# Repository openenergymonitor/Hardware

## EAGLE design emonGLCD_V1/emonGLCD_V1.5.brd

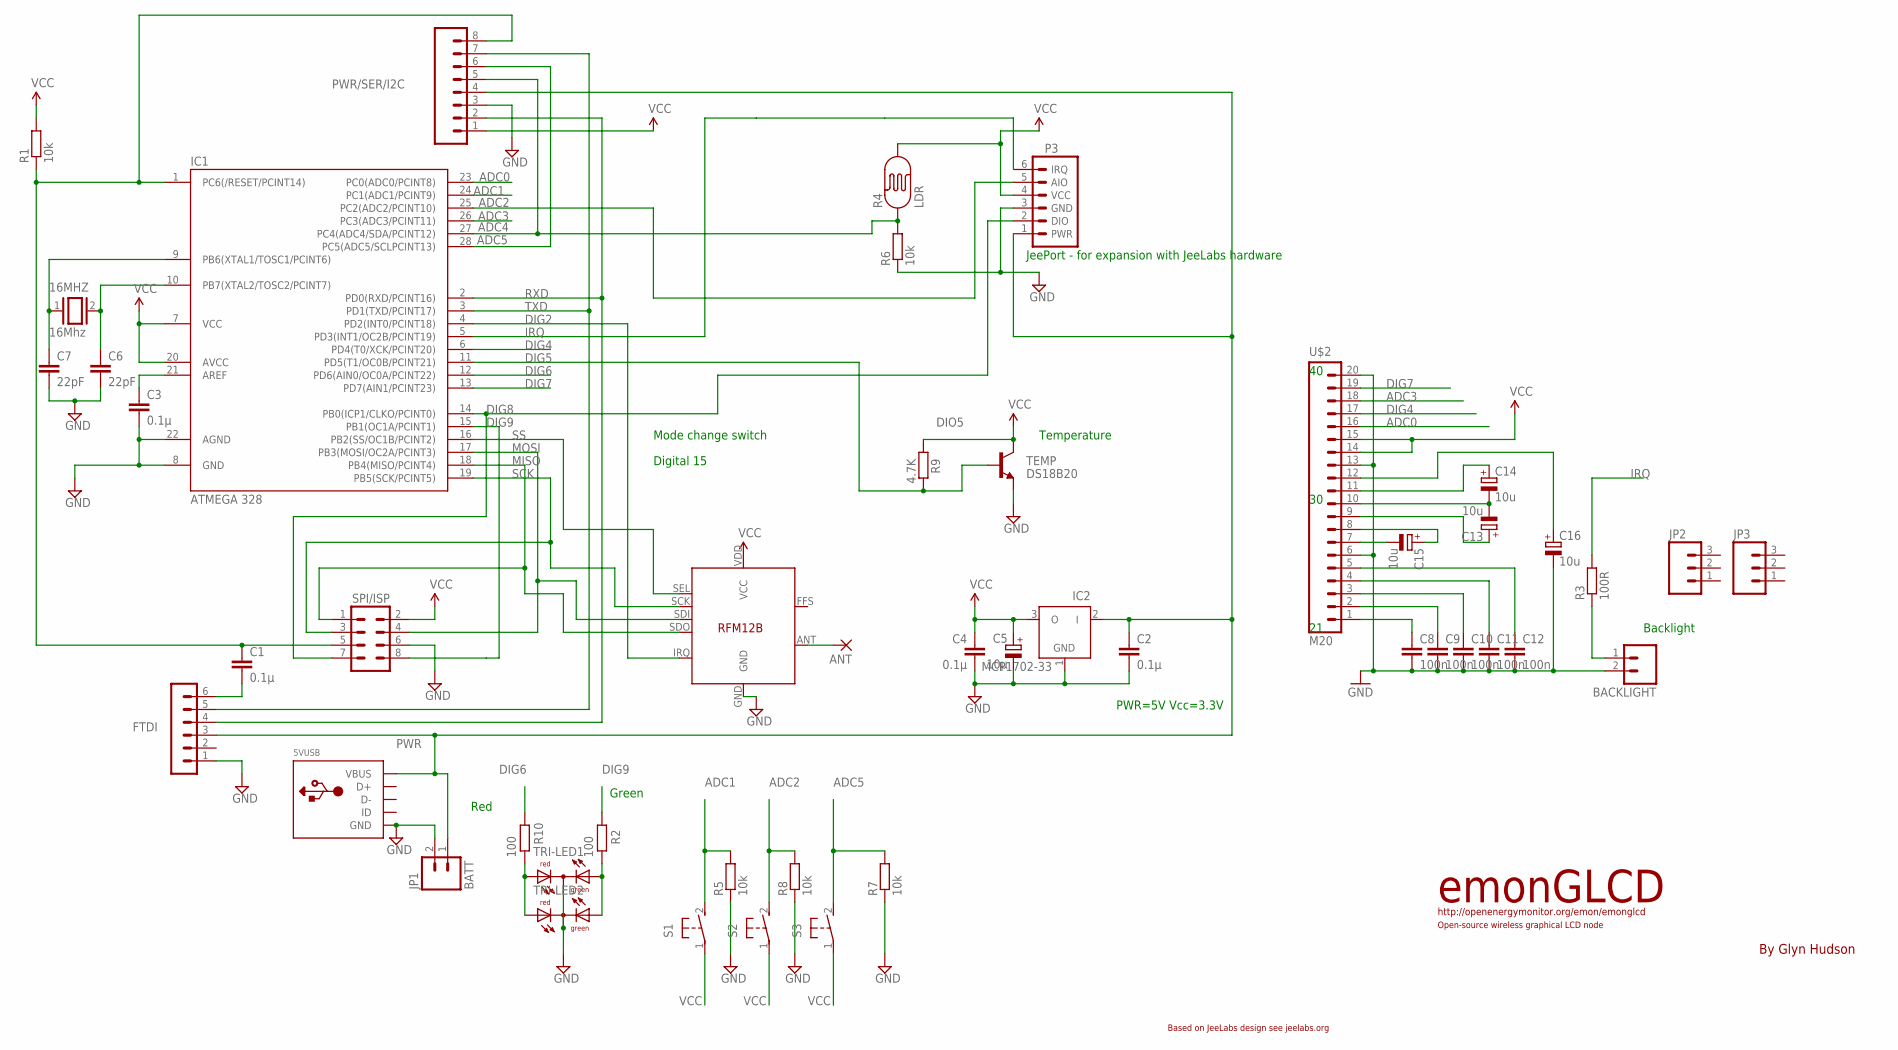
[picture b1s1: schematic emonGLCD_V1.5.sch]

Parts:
5VUSB: USBMOLEX; USB-MINIB-THM-MOLEX
16MHZ: 16Mhz; QS
ANT: 1,6/0,8
BACKLIGHT: M02PTH; 1X02
C1, C2, C3, C4: 0.1µ; C025-024X044
C5: 10µ; E1,8-4
C6, C7: 22pF; C2.5-2
C8, C9, C10, C11, C12: 100n; C2.5-2
C13, C14, C15, C16: 10u; E1,8-4
FTDI: FTDI; MA06-1
IC1: ATMEGA 328; DIL28-3
IC2: MCP1702-33; TO92
JP1: BATT; 1X02_LOCK_LONGPADS
JP2, JP3: M03PTH; 1X03
P3: JEEPORT; PORT6PIN
PWR/SER/I2C: M08; 1X08
R1, R5, R6, R7, R8: 10k; 0204/7
R2, R10: 100; 0204/7
R3: 100R; 0204/7
R4: LDR; PHOTOCELL
R9: 4.7K; 0204/7
S1, S2, S3: 31-XX; B3F-31XX
SV7: SPI/ISP; MA04-2
TEMP: DS18B20; TO-92
TRI-LED1, TRI-LED2: DUOLED5MM
U$1: RFM12B
U$2: M20; 1X20

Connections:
ADC0: IC1.23 (PC0(ADC0/PCINT8)), U$2.16
ADC1: IC1.24 (PC1(ADC1/PCINT9)), R5.2, S1.2 (S)
ADC2: IC1.25 (PC2(ADC2/PCINT10)), P3.5 (AIO), R8.2, S2.2 (S)
ADC3: IC1.26 (PC3(ADC3/PCINT11)), U$2.18
ADC4: IC1.27 (PC4(ADC4/SDA/PCINT12)), PWR/SER/I2C.5, R4.1, R6.2
ADC5: IC1.28 (PC5(ADC5/SCLPCINT13)), PWR/SER/I2C.6, R7.2, S3.2 (S)
DIG2: IC1.4 (PD2(INT0/PCINT18)), U$1.IRQ
DIG4: IC1.6 (PD4(T0/XCK/PCINT20)), U$2.17
DIG5: IC1.11 (PD5(T1/OC0B/PCINT21)), R9.2, TEMP.2 (B)
DIG6: IC1.12 (PD6(AIN0/OC0A/PCINT22)), R10.2
DIG7: IC1.13 (PD7(AIN1/PCINT23)), U$2.19
DIG8: IC1.14 (PB0(ICP1/CLKO/PCINT0)), P3.2 (DIO), SV7.7
DIG9: IC1.15 (PB1(OC1A/PCINT1)), R2.2, SV7.8
GND: 5VUSB.GND, BACKLIGHT.2, C2.2, C3.2, C4.2, C5.-, C6.2, C7.2, C8.2, C9.2, C10.2, C11.2, C12.2, C16.-, FTDI.1, IC1.8 (GND), IC1.22 (AGND), IC2.1 (GND), JP1.2, P3.3 (GND), PWR/SER/I2C.3, R5.1, R6.1, R7.1, R8.1, SV7.6, TEMP.1 (E), TRI-LED1.K (C), TRI-LED2.K (C), U$1.GND, U$2.6, U$2.13, U$2.20
IRQ: IC1.5 (PD3(INT1/OC2B/PCINT19)), P3.6 (IRQ), R3.2
MISO: IC1.18 (PB4(MISO/PCINT4)), SV7.1, U$1.SDO
MOSI: IC1.17 (PB3(MOSI/OC2A/PCINT3)), SV7.4, U$1.SDI
unnamed: 16MHZ.2, C6.1, IC1.10 (PB7(XTAL2/TOSC2/PCINT7))
unnamed: C8.1, U$2.1
unnamed: C9.1, U$2.2
unnamed: C13.-, C14.-, U$2.10
unnamed: C10.1, U$2.3
unnamed: C11.1, U$2.4
unnamed: C12.1, U$2.5
unnamed: R10.1, TRI-LED1.AR, TRI-LED2.AR
unnamed: 16MHZ.1, C7.1, IC1.9 (PB6(XTAL1/TOSC1/PCINT6))
unnamed: ANT.1, U$1.ANT
unnamed: R2.1, TRI-LED1.AG, TRI-LED2.AG
unnamed: C1.2, FTDI.6
unnamed: BACKLIGHT.1, R3.1
unnamed: C3.1, IC1.21 (AREF)
unnamed: C14.+, U$2.11
unnamed: C13.+, U$2.9
unnamed: C15.-, U$2.7
unnamed: C15.+, U$2.8
unnamed: C16.+, U$2.12
PWR: 5VUSB.VBUS, C2.1, FTDI.3, IC2.2 (I), JP1.1, P3.1 (PWR), PWR/SER/I2C.4
RST: C1.1, IC1.1 (PC6(/RESET/PCINT14)), PWR/SER/I2C.8, R1.1, SV7.5
RXD: FTDI.4, IC1.2 (PD0(RXD/PCINT16)), PWR/SER/I2C.2
SCK: IC1.19 (PB5(SCK/PCINT5)), SV7.3, U$1.SCK
SS: IC1.16 (PB2(SS/OC1B/PCINT2)), U$1.SEL
TXD: FTDI.5, IC1.3 (PD1(TXD/PCINT17)), PWR/SER/I2C.7
VCC: C4.1, C5.+, IC1.7 (VCC), IC1.20 (AVCC), IC2.3 (O), P3.4 (VCC), PWR/SER/I2C.1, R1.2, R4.2, R9.1, S1.1, S2.1, S3.1, SV7.2, TEMP.3 (C), U$1.VDD (VCC), U$2.14, U$2.15

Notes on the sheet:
PWR=5V Vcc=3.3V
Temperature
http://openenergymonitor.org/emon/emonglcd
Open-source wireless graphical LCD node
emonGLCD
By Glyn Hudson
Based on JeeLabs design see jeelabs.org
DIO5
Backlight
Mode change switch
Digital 15
JeePort - for expansion with JeeLabs hardware
Red
Green

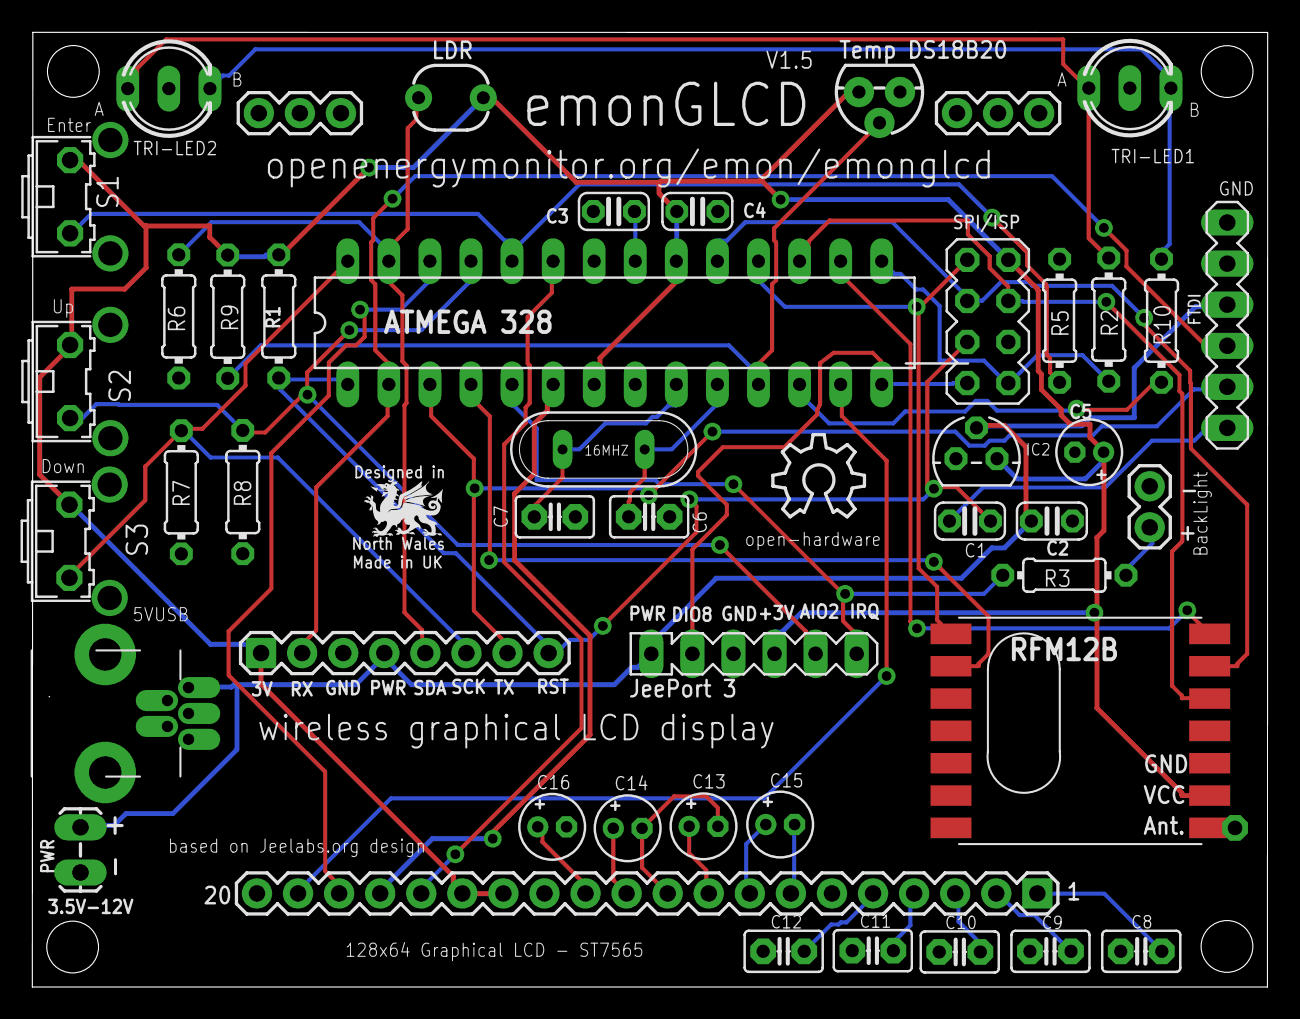
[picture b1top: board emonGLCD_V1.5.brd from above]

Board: 2 copper layers, 76.4 x 59.0 mm, 48 parts (1 on the bottom side), 43 nets.

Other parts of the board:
U$3: Open-source Hardware; OSHW_8X200_NOTEXT

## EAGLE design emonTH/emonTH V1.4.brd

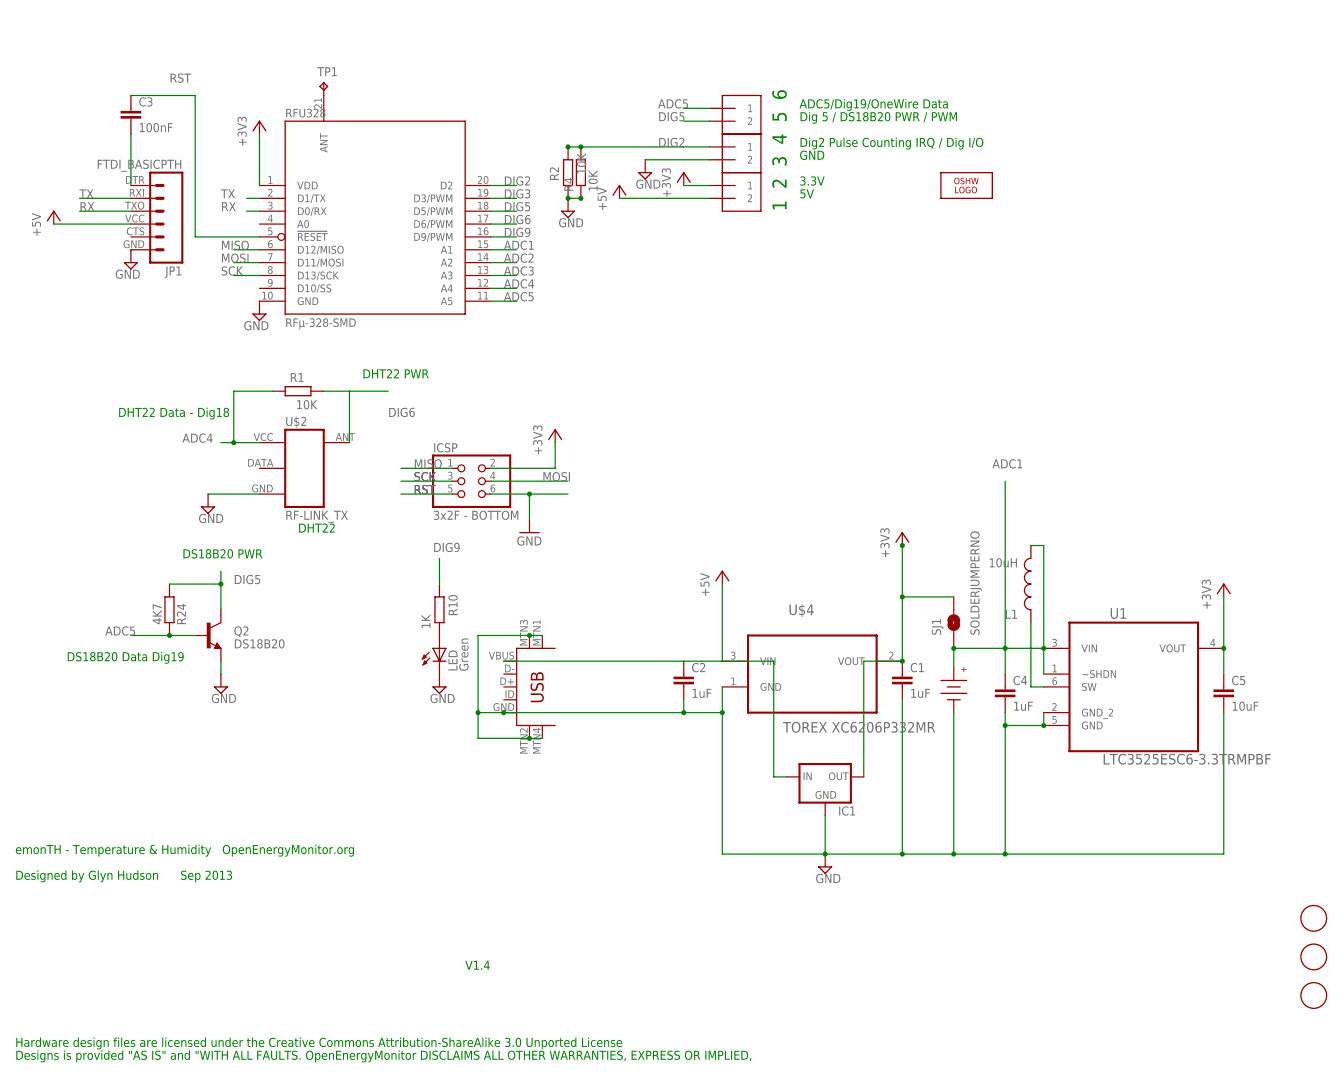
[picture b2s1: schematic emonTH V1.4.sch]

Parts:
C1, C2, C4: 1uF; C0603
C3: 100nF; C0603
C5: 10uF; C0603
IC1: 78XXS
ICSP: 3x2F - BOTTOM; 2X03
J1, J2, J3: 1X2-3.5MM
JP1: FTDI_BASICPTH; FTDI_BASIC
L1: 10uH; 1210
LED: Green; CHIP-LED0805
LOGO1: OSHW_LOGO_10MILX0200-NT; OSHW_10X200_NOTEXT
Q2: DS18B20; TO-92
R1, R2: 10K; R0603
R4: 10K; 0204/7
R10: 1K; R0603
R24: 4K7; R0603
RFU328: RFµ-328-SMD; RFµ-328-LANDING
SJ1: SOLDERJUMPERNO; SJ_2S-NO
TP1: TPPAD1-20; P1-20
U1: LTC3525ESC6-3.3TRMPBF; SOT65P210X100-6N
U$1, U$6, U$7: FIDUCIAL; FIDUCIAL_1MM
U$2: RF-LINK_TX
U$3: 3V; AAA_PCB_HOLDER
U$4: TOREX XC6206P332MR; SOT95P237X112-3N
U$5: USB-MINIB-5PIN; USB-MINIB-CISECO

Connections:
+3V3: C1.1, C5.1, IC1.OUT, ICSP.2, J3.1, RFU328.1 (VDD), SJ1.2, U1.4 (VOUT), U$4.2 (VOUT)
+5V: C2.1, IC1.IN, J3.2, JP1.VCC (4), U$4.3 (VIN), U$5.VBUS
ADC1: C4.1, L1.2, RFU328.15 (A1), SJ1.1, U1.1 (~SHDN), U1.3 (VIN), U$3.+
ADC2: RFU328.14 (A2)
ADC3: RFU328.13 (A3)
ADC4: R1.2, RFU328.12 (A4), U$2.VCC (+5V)
ADC5: J1.1, Q2.2 (B), R24.2, RFU328.11 (A5)
DIG2: J2.1, R2.1, R4.2, RFU328.20 (D2)
DIG3: RFU328.19 (D3/PWM)
DIG5: J1.2, Q2.3 (C), R24.1, RFU328.18 (D5/PWM)
DIG6: R1.1, RFU328.17 (D6/PWM), U$2.ANT
DIG9: R10.2, RFU328.16 (D9/PWM)
GND: C1.2, C2.2, C4.2, C5.2, IC1.GND, ICSP.6, J2.2, JP1.GND (6), LED.C, Q2.1 (E), R2.2, R4.1, RFU328.10 (GND), U1.2 (GND_2), U1.5 (GND), U$2.GND, U$3.-, U$4.1 (GND), U$5.GND, U$5.MTN1 (MTN2), U$5.MTN2 (MTN3), U$5.MTN3 (MTN1), U$5.MTN4
MISO: ICSP.1, RFU328.6 (D12/MISO)
MOSI: ICSP.4, RFU328.7 (D11/MOSI)
unnamed: RFU328.21 (ANT), TP1.TP
unnamed: C3.2, JP1.DTR (1)
unnamed: L1.1, U1.6 (SW)
unnamed: LED.A, R10.1
RST: C3.1, ICSP.5, RFU328.5 (!RESET)
RX: JP1.TXO (3), RFU328.3 (D0/RX)
SCK: ICSP.3, RFU328.8 (D13/SCK)
TX: JP1.RXI (2), RFU328.2 (D1/TX)

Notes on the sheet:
emonTH - Temperature & Humidity OpenEnergyMonitor.org
Designed by Glyn Hudson Sep 2013
V1.4
DS18B20 PWR
DS18B20 Data Dig19
ADC5/Dig19/OneWire Data
Dig 5 / DS18B20 PWR / PWM
Dig2 Pulse Counting IRQ / Dig I/O
GND
3.3V
DHT22 PWR
DHT22
1 2 3 4 5 6
DHT22 Data - Dig18
Hardware design files are licensed under the Creative Commons Attribution-ShareAlike 3.0 Unported License
Designs is provided "AS IS" and "WITH ALL FAULTS. OpenEnergyMonitor DISCLAIMS ALL OTHER WARRANTIES, EXPRESS OR IMPLIED,

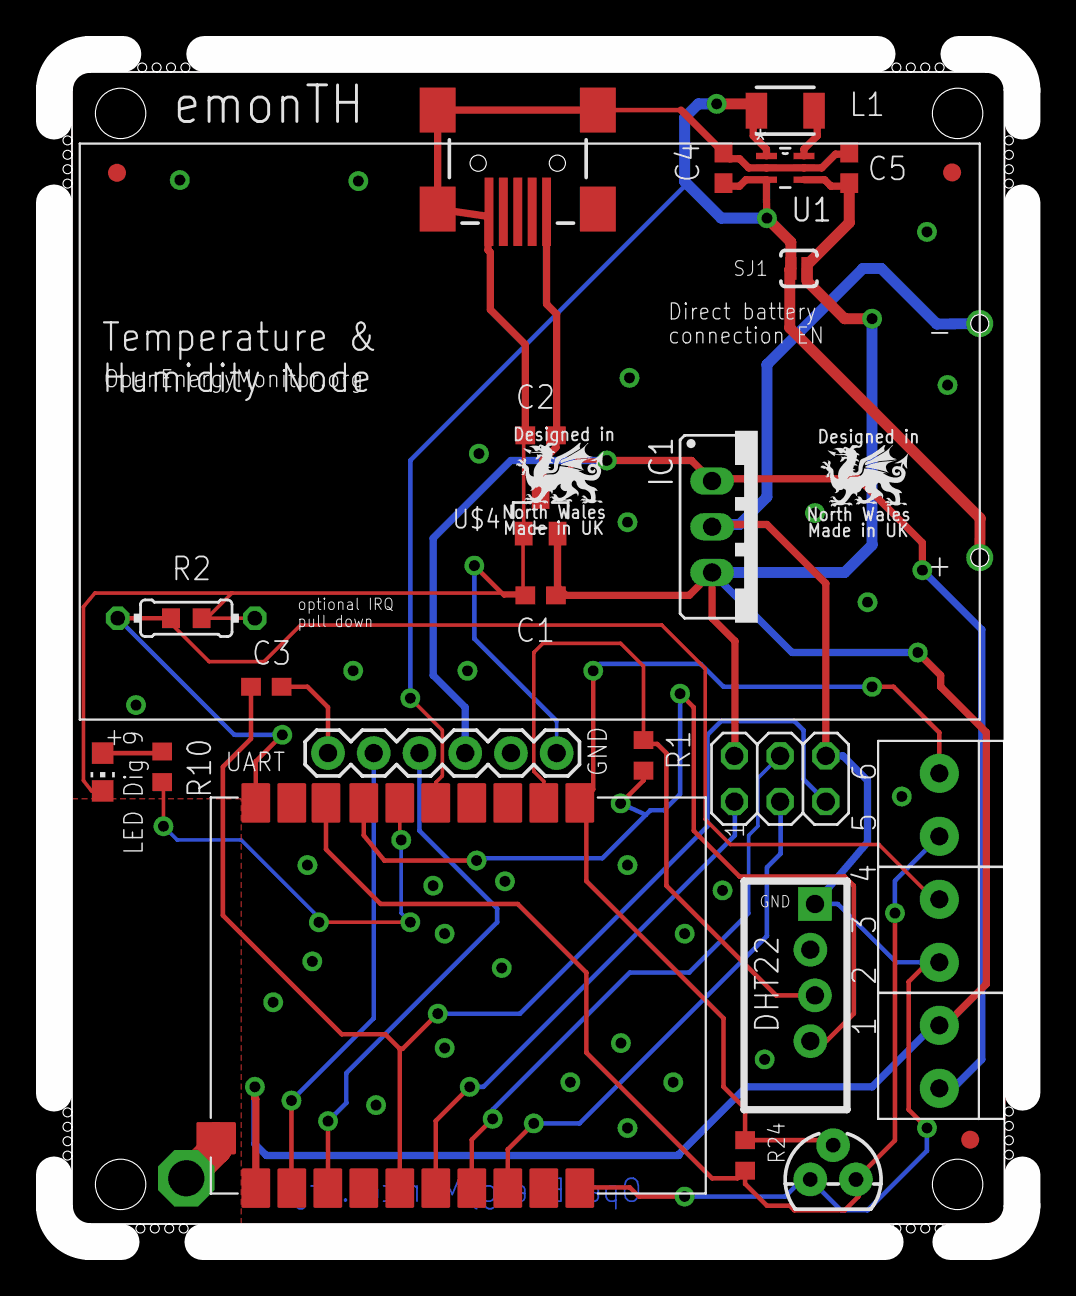
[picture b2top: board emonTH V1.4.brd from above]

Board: 2 copper layers, 53.8 x 66.0 mm, 31 parts (1 on the bottom side), 20 nets.

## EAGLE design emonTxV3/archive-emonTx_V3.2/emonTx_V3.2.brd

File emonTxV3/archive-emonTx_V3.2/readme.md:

# emonTx V3.2

emonTx low power wireless energy monitoring node. 

[http://shop.openenergymonitor.com/emontx-v3/]([http://shop.openenergymonitor.com/emontx-v3/])

[http://openenergymonitor.org/emon/modules/emonTxV3](http://openenergymonitor.org/emon/modules/emonTxV3)

[http://wiki.openenergymonitor.org/index.php?title=EmonTx_V3](http://wiki.openenergymonitor.org/index.php?title=EmonTx_V3)

### Schematic

### Board

### Open Hardware

Hardware designs (schematics and CAD) files are licensed under the [Creative Commons Attribution-ShareAlike 3.0 Unported License](http://creativecommons.org/licenses/by-sa/3.0/) and follow the terms of the [OSHW (Open-source hardware) Statement of Principles 1.0.](http://freedomdefined.org/OSHW)

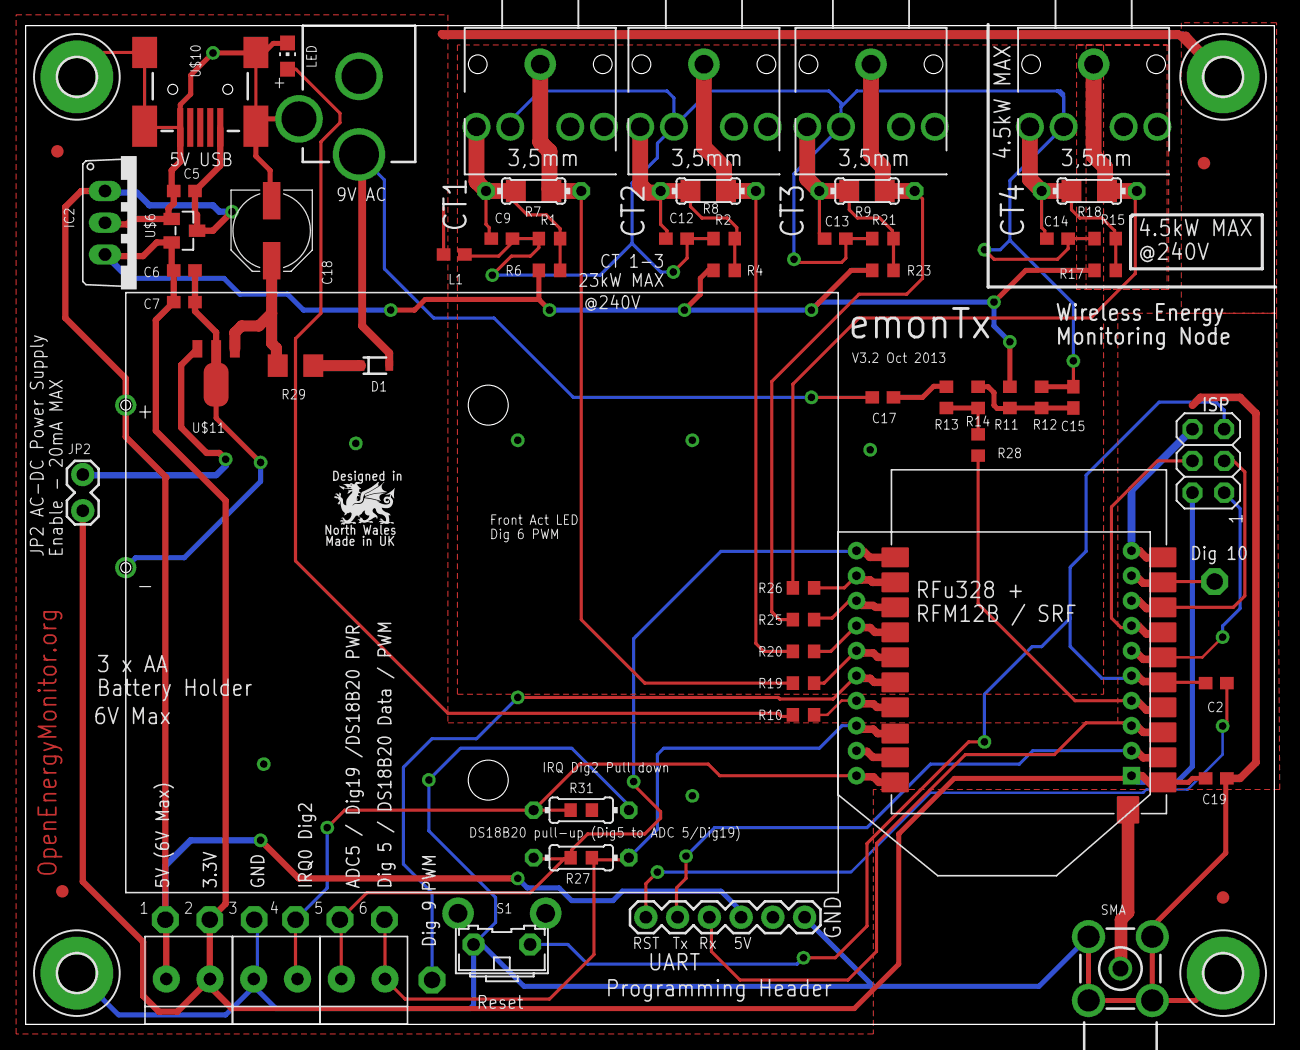
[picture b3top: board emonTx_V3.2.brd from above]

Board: 2 copper layers, 99.9 x 79.9 mm, 83 parts (1 on the bottom side), 40 nets.

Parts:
C2, C7, C19: 100nF; C0603
C5, C6, C17: 1uF 6V; C0603
C9, C12, C13, C14, C15: 10uF 6V; C0603
C18: 47uF 16V; PANASONIC_D
CN1: AC 9V; DCJACK_2MM_PTH
CT1, CT2, CT3, CT4: STEREOJACK; STX3100
D1: 1N4148; SOD-323
H1, H2, H3, H4: MOUNT-PAD-ROUND3.0; 3,0-PAD
IC2: 7805; TO220V
ISP: 3x2F - BOTTOM; 2X03
J1, J2, J4: 1X2-3.5MM
JP1: FTDI; FTDI_BASIC
JP2: 1X02_LOCK
L1: 0603
LED1: Red 1.85V; CHIP-LED0805
LOGO1: OSHW_LOGO_6MILX0200-NT; OSHW_6X200_NOTEXT
R1, R2, R4, R6, R11, R12, R15, R17, R21, R23: 470K; R0603
R3, R5, R22: 22R; 0204/7
R7, R8, R9: 22R; R1206
R10, R19, R20, R25, R26, R28: 1K; R0603
R13: 120K; R0603
R14, R31: 10K; R0603
R16: 120R; 0204/7
R18: 120R; R1206
R24: 4K7; 0204/7
R27: 4K7; R0603
R29: 56R 0.25W; R1206
R30: 10K; 0204/7
RFU: RFµ-328-SMD; RFµ-328-LANDING
S1: B3F-31XX
SMA: BU-SMA-H
TP1, TP3, TP4, TP5, TP6, TP7, TP8, TP9: TPPAD1-13; P1-13
U$1, U$4, U$5, U$7: FIDUCIAL; FIDUCIAL_1MM
U$3: 4.5V; AAA_PCB_HOLDER
U$6: TOREX XC6206P332MR; SOT95P237X112-3N
U$9: XBEE
U$10: USB-MINIB-5PIN; USB-MINIB-CISECO
U$11: MCP1754; SOT89

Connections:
3.3V: C6.2, C7.2, C19.2, IC2.3, ISP.2, J4.1, JP2.2, R4.2, R6.2, R11.2, R17.2, R23.2, RFU.1, TP6.TP, U$6.2, U$9.1
+5V: C5.2, IC2.1, J4.2, JP1.VCC, TP7.TP, U$3.+, U$6.3, U$10.VBUS
AC: C17.2, CN1.PWR, D1.2
ADC0: R28.1, RFU.4, U$9.4
ADC1: R19.2, RFU.15, U$9.15
ADC2: R20.2, RFU.14, U$9.14
ADC3: R25.2, RFU.13, U$9.13
ADC4: R26.2, RFU.12, U$9.12
ADC5: J2.2, R24.2, R27.2, RFU.11, TP3.TP, U$9.11
AGND: C9.2, C12.2, C13.2, C14.2, C15.2, CT1.4, CT2.4, CT3.4, CT4.4, L1.1, R1.2, R2.2, R12.1, R15.2, R21.2
DIG2: J1.1, R30.1, R31.1, RFU.20, TP4.TP, U$9.20
DIG3: RFU.19, U$9.19
DIG5: J2.1, R24.1, R27.1, RFU.18, TP1.TP, U$9.18
DIG6: R10.2, RFU.17, U$9.17
DIG9: RFU.16, TP8.TP, U$9.16
GND: C5.1, C6.1, C7.1, C18.-, C19.1, CN1.GND, CN1.GNDBREAK, H1.B3,0, H2.B3,0, H3.B3,0, H4.B3,0, IC2.2, ISP.6, J1.2, JP1.GND, L1.2, LED1.C, R30.2, R31.2, RFU.10, S1.1, SMA.2, SMA.3, SMA.4, SMA.5, TP5.TP, U$3.-, U$6.1, U$9.10, U$10.GND, U$10.MTN1, U$10.MTN2, U$10.MTN3, U$10.MTN4, U$11.2, U$11.2.1
MISO: ISP.1, RFU.6, U$9.6
MOSI: ISP.4, RFU.7, U$9.7
unnamed: CT1.1, R5.2, R7.2, R19.1
unnamed: C13.1, CT3.5, R9.1, R21.1, R22.1, R23.1
unnamed: R13.2, R14.1, R28.2
unnamed: JP2.1, U$11.3
unnamed: C18.+, R29.2, U$11.1
unnamed: C17.1, R13.1
unnamed: CT4.1, R16.2, R18.2, R26.1
unnamed: C2.1, JP1.DTR
unnamed: CT2.1, R3.2, R8.2, R20.1
unnamed: RFU.21, SMA.1
unnamed: D1.1, R29.1
unnamed: CT3.1, R9.2, R22.2, R25.1
unnamed: C12.1, CT2.5, R2.1, R3.1, R4.1, R8.1
unnamed: C15.1, R11.1, R12.2, R14.2
unnamed: C14.1, CT4.5, R15.1, R16.1, R17.1, R18.1
unnamed: C9.1, CT1.5, R1.1, R5.1, R6.1, R7.1
unnamed: LED1.A, R10.1
RST: C2.2, ISP.5, RFU.5, S1.2, U$9.5
RX: JP1.TXO, RFU.3, U$9.3
SCK: ISP.3, RFU.8, U$9.8
SS: RFU.9, TP9.TP, U$9.9
TX: JP1.RXI, RFU.2, U$9.2

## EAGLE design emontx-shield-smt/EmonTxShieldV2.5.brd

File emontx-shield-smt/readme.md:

## moved to https://github.com/openenergymonitor/emontx-shield

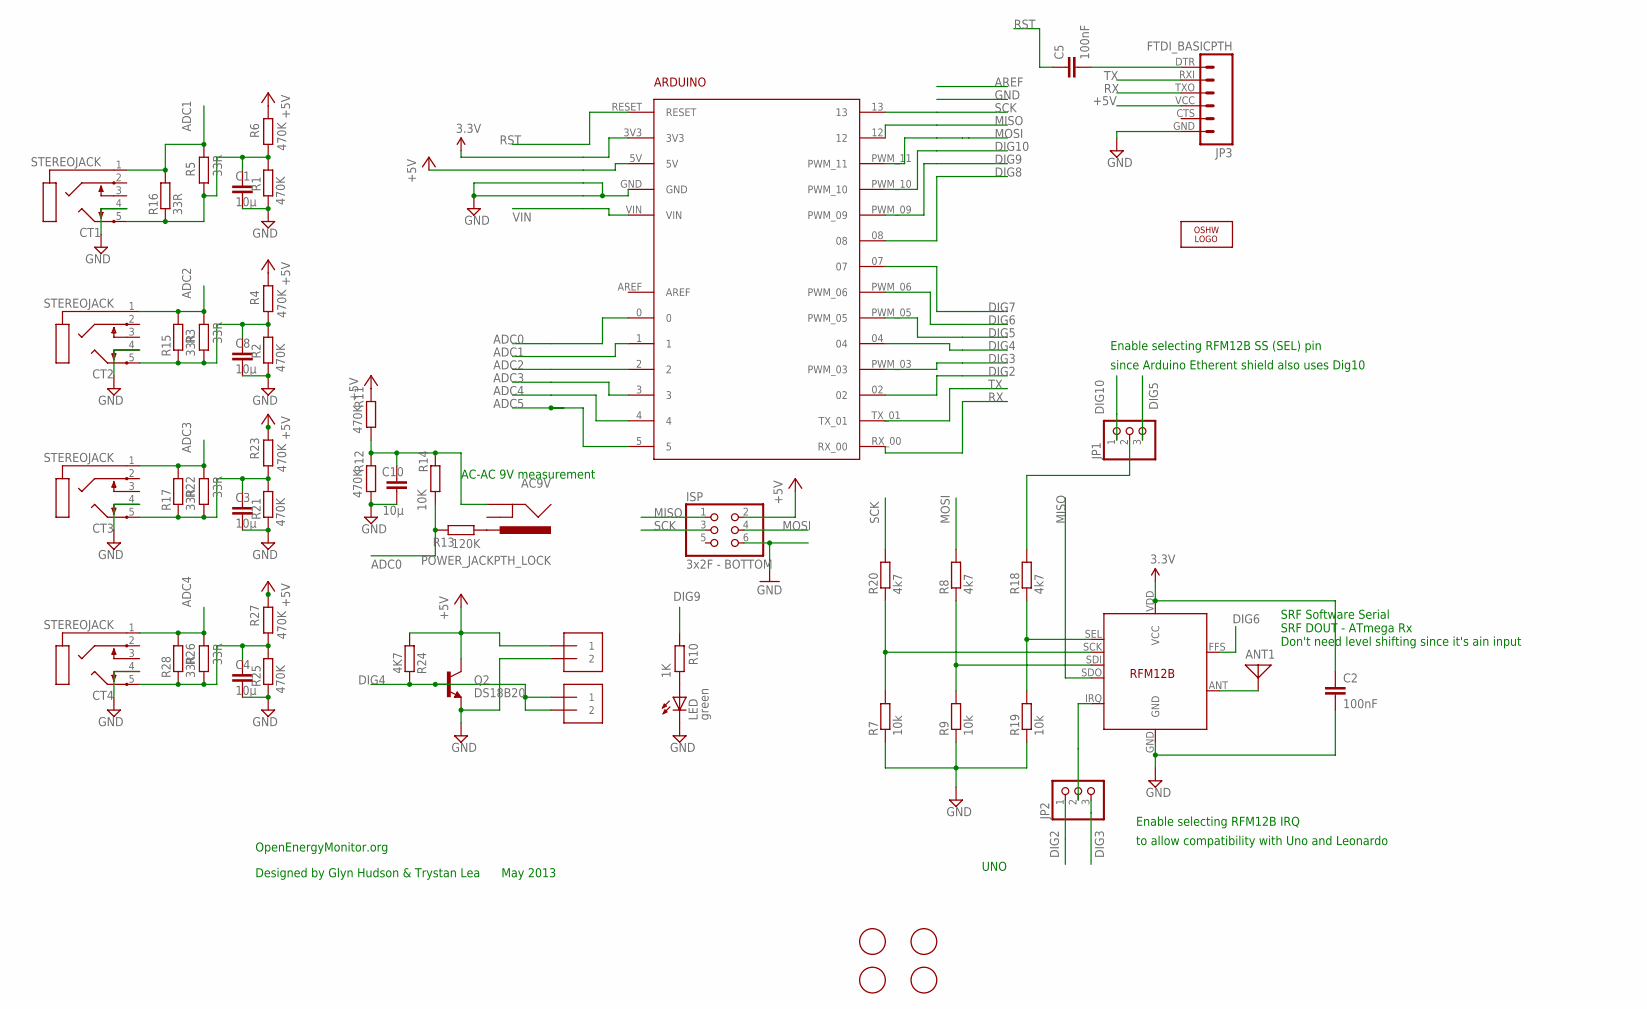
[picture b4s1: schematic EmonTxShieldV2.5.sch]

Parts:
AC9V: POWER_JACKPTH_LOCK; POWER_JACK_PTH_LOCK
ANT1: ANTENNA; PAD-01
ARDUINO1: ARDUINO2
C1, C3, C4, C8, C10: 10µ; C0603
C2, C5: 100nF; C0603
CT1, CT2, CT3, CT4: STEREOJACK; STX3100
ISP: 3x2F - BOTTOM; 2X03
J1, J2: 1X2-3.5MM
JP1, JP2: PINHD-1X3; 1X03
JP3: FTDI_BASICPTH; FTDI_BASIC
LED: green; CHIPLED_0805
LOGO1: OSHW_LOGO_10MILX0200-NT; OSHW_10X200_NOTEXT
Q2: DS18B20; TO-92
R1, R2, R4, R6, R11, R12, R21, R23, R25, R27: 470K; R0603
R3, R5, R22, R26: 33R; 0204/7
R7, R9, R19: 10k; R0603
R8, R18, R20: 4k7; R0603
R10: 1K; R0603
R13: 120K; R0603
R14: 10K; R0603
R15, R16, R17, R28: 33R; R1206
R24: 4K7; R0603
U$1, U$3, U$4, U$5: FIDUCIAL; FIDUCIAL_1MM
U$2: RFM12B

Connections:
3.3V: ARDUINO1.3V3, C2.1, U$2.VDD (VCC)
+5V: ARDUINO1.5V, ISP.2, J1.1, JP3.VCC (4), Q2.3 (C), R4.2, R6.2, R11.2, R23.2, R24.1, R27.2
ADC0: ARDUINO1.0, R13.2, R14.1
ADC1: ARDUINO1.1, CT1.1, R5.2, R16.2
ADC2: ARDUINO1.2, CT2.1, R3.2, R15.2
ADC3: ARDUINO1.3, CT3.1, R17.2, R22.2
ADC4: ARDUINO1.4, CT4.1, R26.2, R28.2
ADC5: ARDUINO1.5
DIG2: ARDUINO1.02, JP2.1
DIG3: ARDUINO1.PWM_03, JP2.3
DIG4: ARDUINO1.04, J2.1, J2.2, Q2.2 (B), R24.2
DIG5: ARDUINO1.PWM_05, JP1.3
DIG6: ARDUINO1.PWM_06, U$2.FFS
DIG7: ARDUINO1.07
DIG8: ARDUINO1.08
DIG9: ARDUINO1.PWM_09, R10.2
DIG10: ARDUINO1.PWM_10, JP1.1
GND: ARDUINO1.GND, C1.2, C2.2, C3.2, C4.2, C8.2, C10.2, CT1.4, CT2.4, CT3.4, CT4.4, ISP.6, J1.2, JP3.GND (6), LED.C, Q2.1 (E), R1.2, R2.2, R7.1, R9.1, R12.1, R19.1, R21.2, R25.2, U$2.GND
MISO: ARDUINO1.12, ISP.1, U$2.SDO
MOSI: ARDUINO1.PWM_11, ISP.4, R8.2
unnamed: JP2.2, U$2.IRQ
unnamed: JP1.2, R18.2
unnamed: C3.1, CT3.5, R17.1, R21.1, R22.1, R23.1
unnamed: C4.1, CT4.5, R25.1, R26.1, R27.1, R28.1
unnamed: AC9V.PWR, R13.1
unnamed: C5.2, JP3.DTR (1)
unnamed: C8.1, CT2.5, R2.1, R3.1, R4.1, R15.1
unnamed: AC9V.GND, C10.1, R11.1, R12.2, R14.2
unnamed: C1.1, CT1.5, R1.1, R5.1, R6.1, R16.1
unnamed: LED.A, R10.1
unnamed: ANT1.1, U$2.ANT
unnamed: R7.2, R20.1, U$2.SCK
unnamed: R8.1, R9.2, U$2.SDI
unnamed: R18.1, R19.2, U$2.SEL
RST: ARDUINO1.RESET, C5.1
RX: ARDUINO1.RX_00, JP3.TXO (3)
SCK: ARDUINO1.13, ISP.3, R20.2
TX: ARDUINO1.TX_01, JP3.RXI (2)
VIN: ARDUINO1.VIN

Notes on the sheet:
AC-AC 9V measurement
Enable selecting RFM12B SS (SEL) pin
since Arduino Etherent shield also uses Dig10
Enable selecting RFM12B IRQ
to allow compatibility with Uno and Leonardo
UNO
OpenEnergyMonitor.org
Designed by Glyn Hudson & Trystan Lea May 2013
SRF Software Serial SRF DOUT - ATmega Rx Don't need level shifting since it's ain input

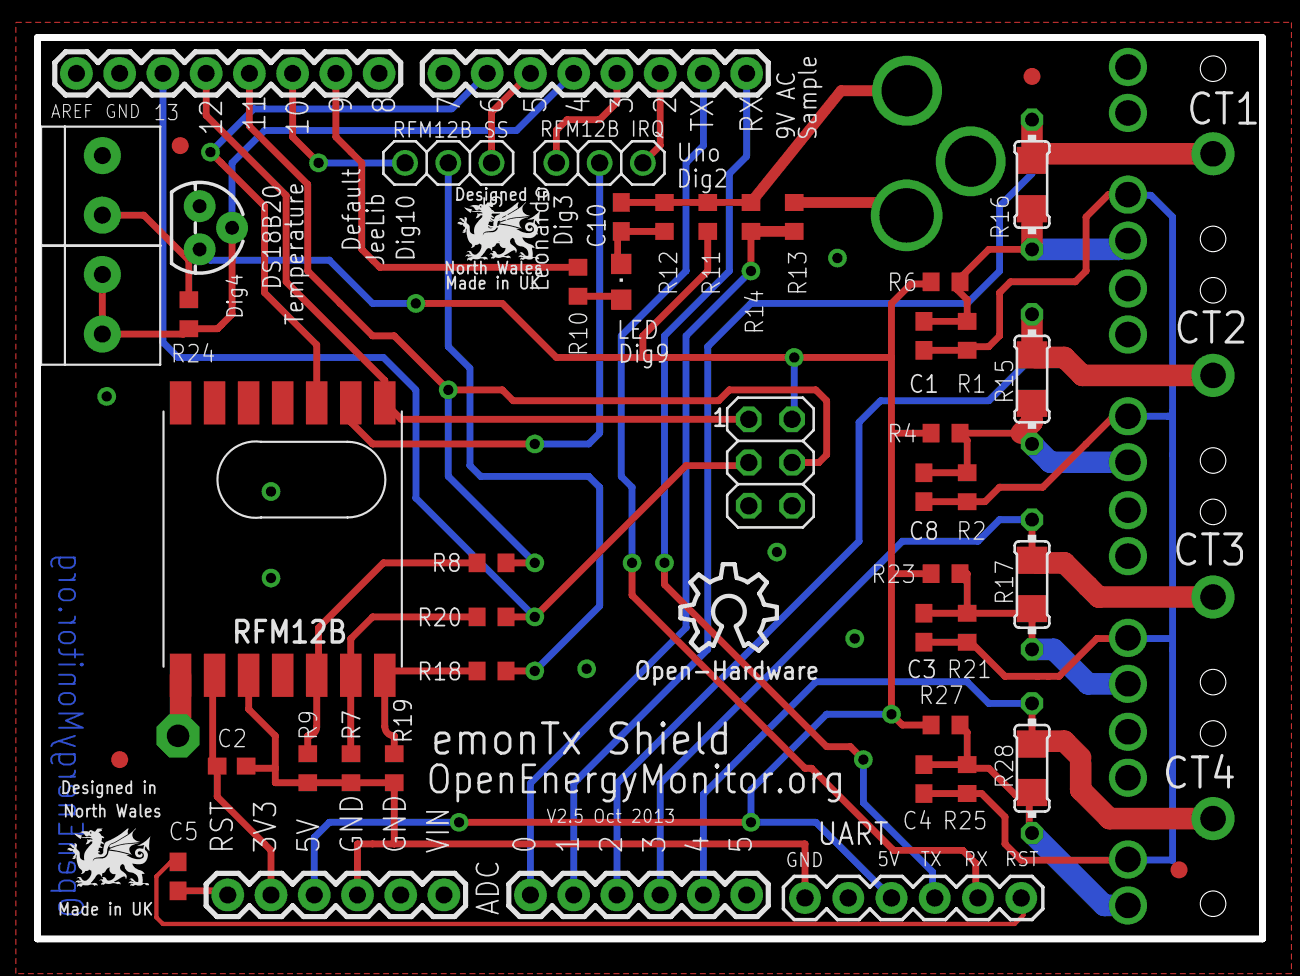
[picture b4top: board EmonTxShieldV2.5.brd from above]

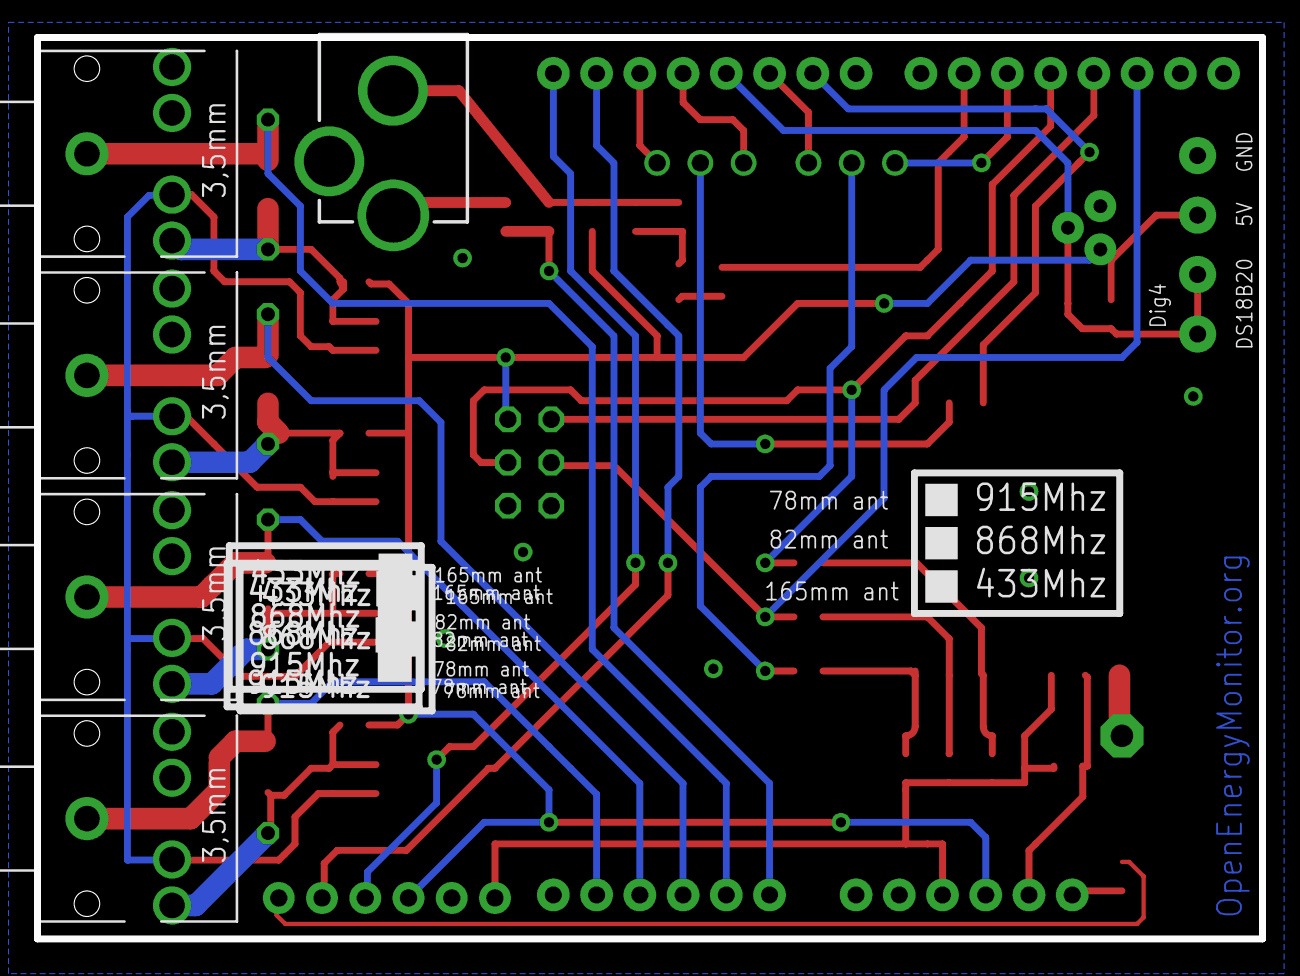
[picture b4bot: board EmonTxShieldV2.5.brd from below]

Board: 2 copper layers, 72.0 x 53.0 mm, 56 parts (5 on the bottom side), 35 nets.

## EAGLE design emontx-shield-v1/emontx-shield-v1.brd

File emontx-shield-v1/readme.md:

## emonTx Shield

**A wireless energy monitoring Arduino compatible shield**

An Arduino Uno and Leonardo compatiable shield with 4 x CT current sensor inputs, 1 x AC voltage sense input, RFM12B 433/868Mhz wireless and DS18B20 digital temperature sensor options.

The shield can un-non-invasively monitor apparent power, real power, power factor and AC RMS mains voltage.

Documentation: [openenergymonitor.org/emon/emontxshield](openenergymonitor.org/emon/emontxshield)

### Eagle schematic and board file

Download both the schematic and board file and open in eagle, click on File > Switch to Board to navigate between schematic view and PCB Board view.

- Schematic: [emontx-shield-v1.sch](emontx-shield-v1.sch)
- Board: [emontx-shield-v1.brd](emontx-shield-v1.brd)
- BOM: [bom.json](bom.json)

### Schematic

### Board

### Open Hardware

Hardware designs (schematics and CAD) files are licensed under the [Creative Commons Attribution-ShareAlike 3.0 Unported License](http://creativecommons.org/licenses/by-sa/3.0/) and follow the terms of the [OSHW (Open-source hardware) Statement of Principles 1.0.](http://freedomdefined.org/OSHW)

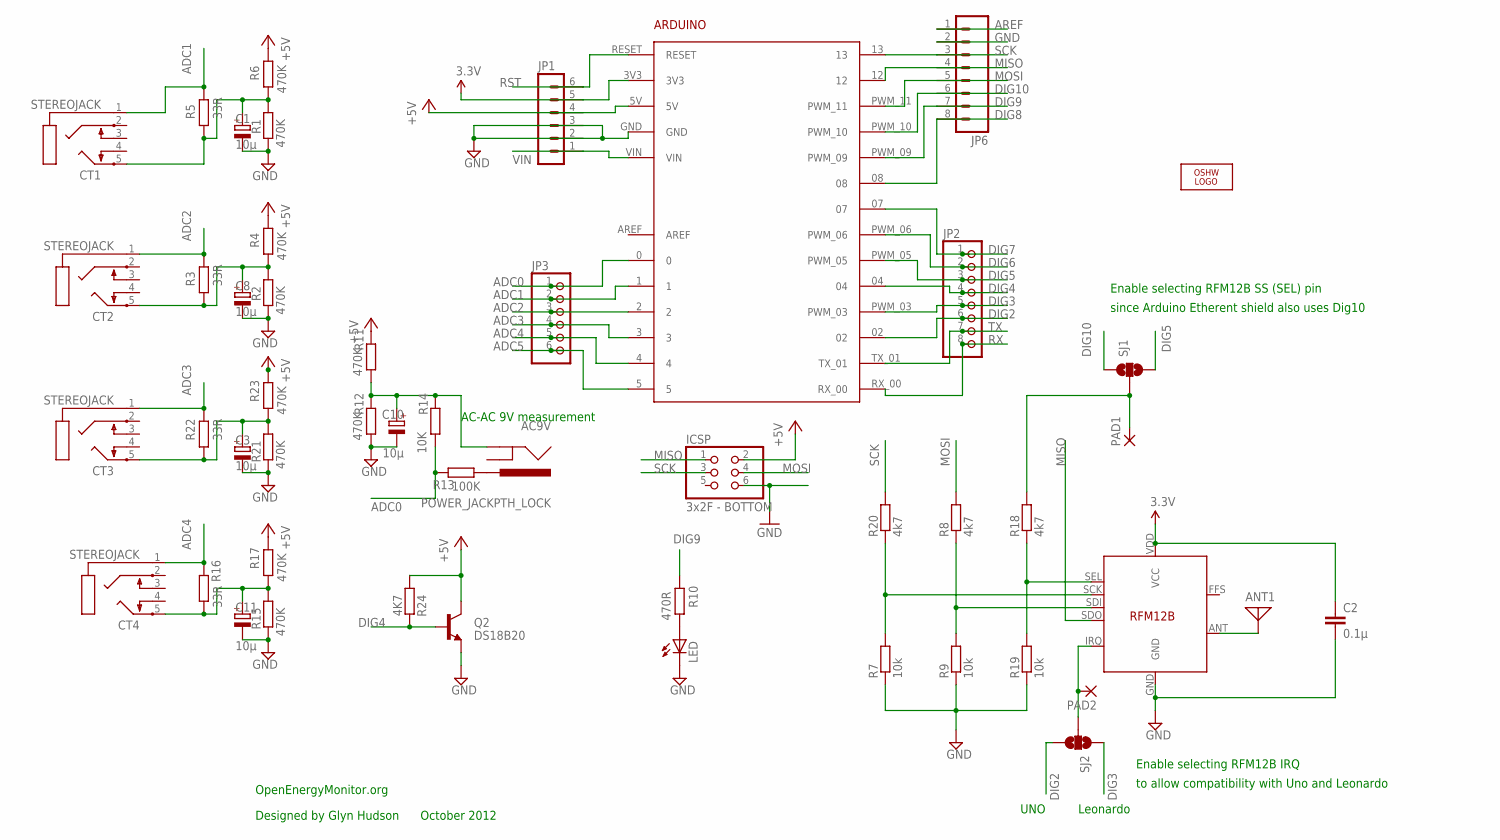
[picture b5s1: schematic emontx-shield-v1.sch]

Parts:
AC9V: POWER_JACKPTH_LOCK; POWER_JACK_PTH_LOCK
ANT1: ANTENNA; PAD-01
ARDUINO1: ARDUINO2
C1, C3, C8, C10, C11: 10µ; E1,8-4
C2: 0.1µ; CAP-PTH-SMALL
CT1, CT2, CT3, CT4: STEREOJACK; STX3100
ICSP: 3x2F - BOTTOM; 2X03
JP1: JEELABS_MA06-1
JP2: PINHD-1X8; 1X08
JP3: PINHD-1X6; 1X06
JP6: SPARKFUN_M08; SPARKFUN_1X08
LED: LED3MM
LOGO1: OSHW_LOGO_10MILX0200-NT; OSHW_10X200_NOTEXT
PAD1, PAD2: JEELABS_1,6/0,8
Q2: DS18B20; TO-92
R1, R2, R4, R6, R11, R12, R15, R17, R21, R23: 470K; 0204/7
R3, R5, R16, R22: 33R; 0204/7
R7, R9, R19: 10k; RESISTOR_0204/7
R8, R18, R20: 4k7; RESISTOR_0204/7
R10: 470R; 0204/7
R13: 100K; 0204/7
R14: 10K; 0204/7
R24: 4K7; 0204/7
SJ1, SJ2: SOLDERJUMPER_2WAYS; SJ_3
U$2: RFM12B

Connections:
3.3V: ARDUINO1.3V3, C2.1, JP1.5, U$2.VDD (VCC)
+5V: ARDUINO1.5V, ICSP.2, JP1.4, Q2.3 (C), R4.2, R6.2, R11.2, R17.2, R23.2, R24.1
ADC0: ARDUINO1.0, JP3.1, R13.2, R14.1
ADC1: ARDUINO1.1, CT1.1, JP3.2, R5.2
ADC2: ARDUINO1.2, CT2.1, JP3.3, R3.2
ADC3: ARDUINO1.3, CT3.1, JP3.4, R22.2
ADC4: ARDUINO1.4, CT4.1, JP3.5, R16.2
ADC5: ARDUINO1.5, JP3.6
AREF: JP6.1
DIG2: ARDUINO1.02, JP2.6, SJ2.3
DIG3: ARDUINO1.PWM_03, JP2.5, SJ2.1
DIG4: ARDUINO1.04, JP2.4, Q2.2 (B), R24.2
DIG5: ARDUINO1.PWM_05, JP2.3, SJ1.3
DIG6: ARDUINO1.PWM_06, JP2.2
DIG7: ARDUINO1.07, JP2.1
DIG8: ARDUINO1.08, JP6.8
DIG9: ARDUINO1.PWM_09, JP6.7, R10.2
DIG10: ARDUINO1.PWM_10, JP6.6, SJ1.1
GND: ARDUINO1.GND, C1.-, C2.2, C3.-, C8.-, C10.-, C11.-, ICSP.6, JP1.2, JP1.3, JP6.2, LED.K (C), Q2.1 (E), R1.2, R2.2, R7.1, R9.1, R12.1, R15.2, R19.1, R21.2, U$2.GND
MISO: ARDUINO1.12, ICSP.1, JP6.4, U$2.SDO
MOSI: ARDUINO1.PWM_11, ICSP.4, JP6.5, R8.2
unnamed: PAD2.1, SJ2.2, U$2.IRQ
unnamed: PAD1.1, R18.2, SJ1.2
unnamed: C3.+, CT3.5, R21.1, R22.1, R23.1
unnamed: AC9V.PWR, R13.1
unnamed: C8.+, CT2.5, R2.1, R3.1, R4.1
unnamed: AC9V.GND, C10.+, R11.1, R12.2, R14.2
unnamed: C11.+, CT4.5, R15.1, R16.1, R17.1
unnamed: C1.+, CT1.5, R1.1, R5.1, R6.1
unnamed: LED.A, R10.1
unnamed: ANT1.1, U$2.ANT
unnamed: R7.2, R20.1, U$2.SCK
unnamed: R8.1, R9.2, U$2.SDI
unnamed: R18.1, R19.2, U$2.SEL
RST: ARDUINO1.RESET, JP1.6
RX: ARDUINO1.RX_00, JP2.8
SCK: ARDUINO1.13, ICSP.3, JP6.3, R20.2
TX: ARDUINO1.TX_01, JP2.7
VIN: ARDUINO1.VIN, JP1.1

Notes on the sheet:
AC-AC 9V measurement
Enable selecting RFM12B SS (SEL) pin
since Arduino Etherent shield also uses Dig10
Enable selecting RFM12B IRQ
to allow compatibility with Uno and Leonardo
UNO
Leonardo
OpenEnergyMonitor.org
Designed by Glyn Hudson October 2012

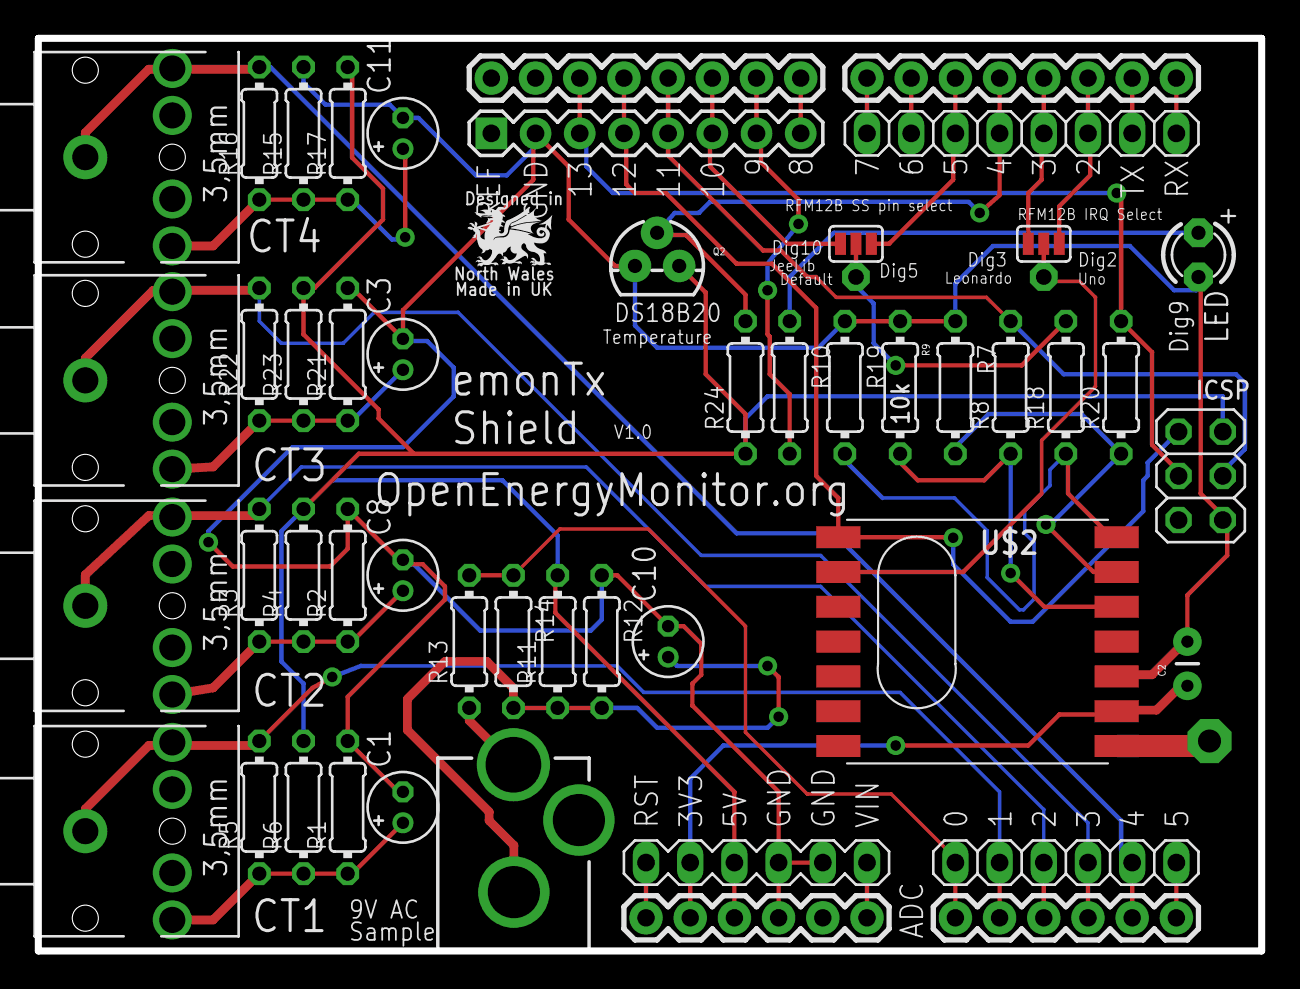
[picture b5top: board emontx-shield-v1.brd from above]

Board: 2 copper layers, 70.3 x 52.5 mm, 50 parts (1 on the bottom side), 38 nets.

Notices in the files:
parts and their libraries:
SparkFun: Licensing: CC v3.0 Share-Alike You are welcome to use this library for commercial purposes.
